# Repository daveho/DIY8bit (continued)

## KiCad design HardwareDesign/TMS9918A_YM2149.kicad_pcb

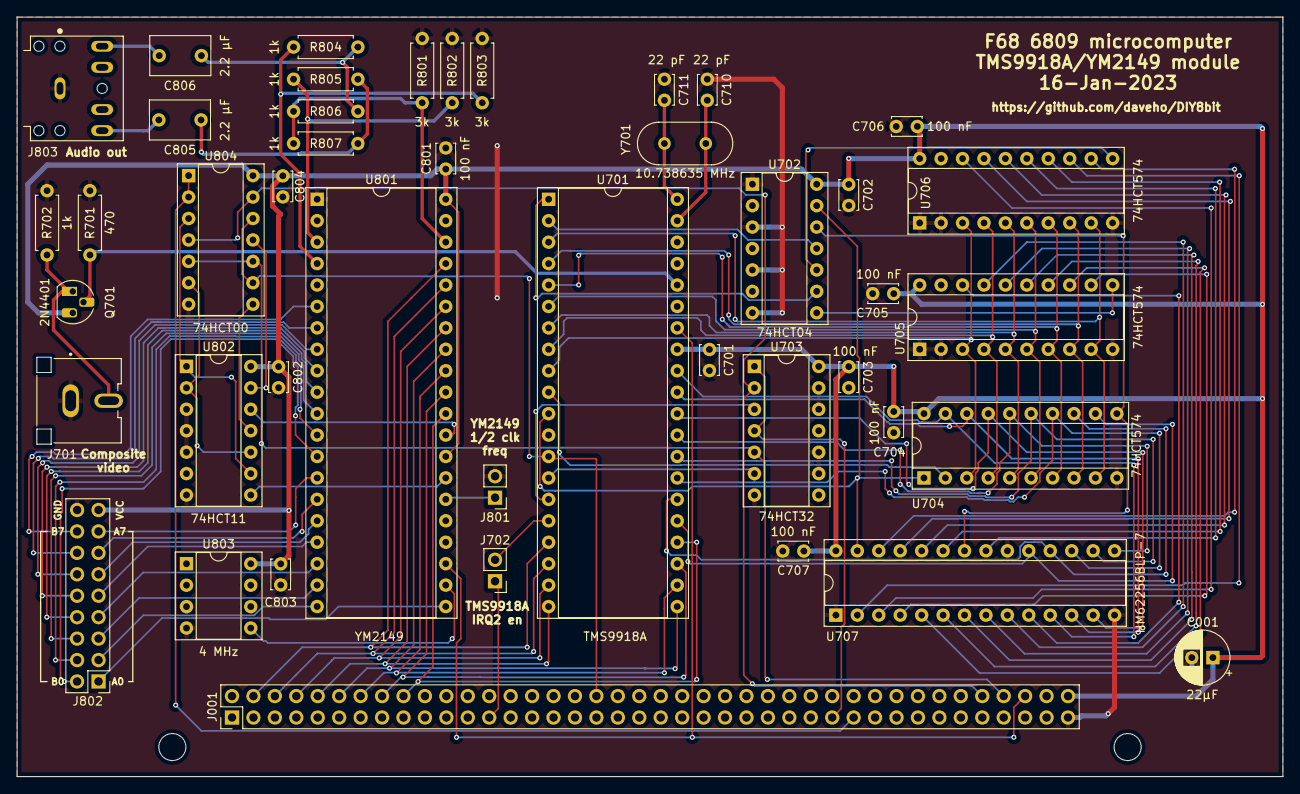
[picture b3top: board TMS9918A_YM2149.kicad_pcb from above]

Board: 2 copper layers, 150.0 x 90.0 mm, 44 parts (0 on the bottom side), 91 nets.

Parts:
C001: 22μF; CP_Radial_D6.3mm_P2.50mm
C701, C702, C703, C704, C705, C706, C707, C801, C802, C803, C804: 100 nF; C_Disc_D3.4mm_W2.1mm_P2.50mm
C710, C711: 22 pF; C_Disc_D3.4mm_W2.1mm_P2.50mm
C805, C806: 2.2 μF; C_Rect_L7.0mm_W4.5mm_P5.00mm
J001: Conn_02x40_Odd_Even; PinHeader_2x40_P2.54mm_Vertical
J701: RCJ-044; CUI_RCJ-044
J702, J801: Conn_01x02; PinHeader_1x02_P2.54mm_Vertical
J802: Conn_02x09_Odd_Even; PinHeader_2x09_P2.54mm_Vertical
J803: SJ1-3525N; CUI_SJ1-3525N
Q701: 2N4401; TO-92_HandSolder
R701: 470; R_Axial_DIN0207_L6.3mm_D2.5mm_P7.62mm_Horizontal
R702, R804, R805, R806, R807: 1k; R_Axial_DIN0207_L6.3mm_D2.5mm_P7.62mm_Horizontal
R801, R802, R803: 3k; R_Axial_DIN0207_L6.3mm_D2.5mm_P7.62mm_Horizontal
U701: TMS9918A; DIP-40_W15.24mm_Socket
U702: 74HCT04; DIP-14_W7.62mm_Socket
U703: 74HCT32; DIP-14_W7.62mm_Socket
U704, U705, U706: 74HCT574; DIP-20_W7.62mm_Socket
U707: HM62256BLP-7; DIP-28_W7.62mm_Socket
U801: YM2149; DIP-40_W15.24mm_Socket
U802: 74HCT11; DIP-14_W7.62mm_Socket
U803: 4 MHz; DIP-8_W7.62mm_Socket
U804: 74HCT00; DIP-14_W7.62mm_Socket
Y701: 10.738635 MHz; Crystal_HC18-U_Vertical

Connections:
/A0: J001.36, U701.13 (MODE), U804.9, U804.12
/D0: J001.4, U701.17 (CD7), U801.37 (DA0)
/D1: J001.6, U701.18 (CD6), U801.36 (DA1)
/D2: J001.8, U701.19 (CD5), U801.35 (DA2)
/D3: J001.10, U701.20 (CD4), U801.34 (DA3)
/D4: J001.12, U701.21 (CD3), U801.33 (DA4)
/D5: J001.14, U701.22 (CD2), U801.32 (DA5)
/D6: J001.16, U701.23 (CD1), U801.31 (DA6)
/D7: J001.18, U701.24 (CD0), U801.30 (DA7)
/TMS9918ADisplay/AD0: U701.10 (AD0), U704.2 (D0)
/TMS9918ADisplay/AD1: U701.9 (AD1), U704.3 (D1), U705.3 (D1), U706.3 (D1)
/TMS9918ADisplay/AD2: U701.8 (AD2), U704.4 (D2), U705.4 (D2), U706.4 (D2)
/TMS9918ADisplay/AD3: U701.7 (AD3), U704.5 (D3), U705.5 (D3), U706.5 (D3)
/TMS9918ADisplay/AD4: U701.6 (AD4), U704.6 (D4), U705.6 (D4), U706.6 (D4)
/TMS9918ADisplay/AD5: U701.5 (AD5), U704.7 (D5), U705.7 (D5), U706.7 (D5)
/TMS9918ADisplay/AD6: U701.4 (AD6), U704.8 (D6), U705.8 (D6), U706.8 (D6)
/TMS9918ADisplay/AD7: U701.3 (AD7), U704.9 (D7), U705.9 (D7), U706.9 (D7)
/TMS9918ADisplay/VA0: U705.18 (Q1), U707.10 (A0)
/TMS9918ADisplay/VA1: U705.17 (Q2), U707.9 (A1)
/TMS9918ADisplay/VA2: U705.16 (Q3), U707.8 (A2)
/TMS9918ADisplay/VA3: U705.15 (Q4), U707.7 (A3)
/TMS9918ADisplay/VA4: U705.14 (Q5), U707.6 (A4)
/TMS9918ADisplay/VA5: U705.13 (Q6), U707.5 (A5)
/TMS9918ADisplay/VA6: U705.12 (Q7), U707.4 (A6)
/TMS9918ADisplay/VA7: U706.18 (Q1), U707.3 (A7)
/TMS9918ADisplay/VA8: U706.17 (Q2), U707.25 (A8)
/TMS9918ADisplay/VA9: U706.16 (Q3), U707.24 (A9)
/TMS9918ADisplay/VA10: U706.15 (Q4), U707.21 (A10)
/TMS9918ADisplay/VA11: U706.14 (Q5), U707.23 (A11)
/TMS9918ADisplay/VA12: U706.13 (Q6), U707.2 (A12)
/TMS9918ADisplay/VA13: U706.12 (Q7), U707.26 (A13)
/TMS9918ADisplay/VD0: U701.32 (RD0), U704.19 (Q0), U707.11 (D0)
/TMS9918ADisplay/VD1: U701.31 (RD1), U704.18 (Q1), U707.12 (D1)
/TMS9918ADisplay/VD2: U701.30 (RD2), U704.17 (Q2), U707.13 (D2)
/TMS9918ADisplay/VD3: U701.29 (RD3), U704.16 (Q3), U707.15 (D3)
/TMS9918ADisplay/VD4: U701.28 (RD4), U704.15 (Q4), U707.16 (D4)
/TMS9918ADisplay/VD5: U701.27 (RD5), U704.14 (Q5), U707.17 (D5)
/TMS9918ADisplay/VD6: U701.26 (RD6), U704.13 (Q6), U707.18 (D6)
/TMS9918ADisplay/VD7: U701.25 (RD7), U704.12 (Q7), U707.19 (D7)
/TMS9918ADisplay/VR/~W: U701.11 (R/~W), U702.13, U704.1 (OE), U707.27 (~WE)
/TMS9918ADisplay/V~R/W: U702.12, U704.11 (Cp), U707.22 (~OE)
/TMS9918ADisplay/~CAS: U701.2 (~CAS), U702.11
/TMS9918ADisplay/~RAS: U701.1 (~RAS), U702.9
/TMS9918ADisplay/~VDPRD: U701.15 (~CSR), U703.3
/TMS9918ADisplay/~VDPWR: U701.14 (~CSW), U703.6
/YM2149_Sound/ANLG_A: R803.1, R804.1, U801.4 (ANLG_A)
/YM2149_Sound/ANLG_B: R802.1, R805.1, U801.3 (ANLG_B)
/YM2149_Sound/ANLG_C: R801.1, R806.1, R807.1, U801.38 (ANLG_C)
/YM2149_Sound/BC1: U801.29 (BC1), U802.12
/YM2149_Sound/BDIR: U801.27 (BDIR), U802.8
/YM2149_Sound/IOA0: J802.1, U801.21 (IOA0)
/YM2149_Sound/IOA1: J802.3, U801.20 (IOA1)
/YM2149_Sound/IOA2: J802.5, U801.19 (IOA2)
/YM2149_Sound/IOA3: J802.7, U801.18 (IOA3)
/YM2149_Sound/IOA4: J802.9, U801.17 (IOA4)
/YM2149_Sound/IOA5: J802.11, U801.16 (IOA5)
/YM2149_Sound/IOA6: J802.13, U801.15 (IOA6)
/YM2149_Sound/IOA7: J802.15, U801.14 (IOA7)
/YM2149_Sound/IOB0: J802.2, U801.13 (IOB0)
/YM2149_Sound/IOB1: J802.4, U801.12 (IOB1)
/YM2149_Sound/IOB2: J802.6, U801.11 (IOB2)
/YM2149_Sound/IOB3: J802.8, U801.10 (IOB3)
/YM2149_Sound/IOB4: J802.10, U801.9 (IOB4)
/YM2149_Sound/IOB5: J802.12, U801.8 (IOB5)
/YM2149_Sound/IOB6: J802.14, U801.7 (IOB6)
/YM2149_Sound/IOB7: J802.16, U801.6 (IOB7)
/YM2149_Sound/RING: C806.1, R804.2, R806.2
/YM2149_Sound/TIP: C805.1, R805.2, R807.2
/~IODEV5: J001.57, U703.1, U703.4
/~IODEV6: J001.59, U804.1, U804.2
/~IRQ2: J001.25, J702.1
/~RMEM: J001.72, U703.2, U804.4, U804.13
/~RST: J001.76, U701.34 (~RESET/SYNC), U801.23 (-RST)
/~WMEM: J001.74, U703.5, U804.5, U804.10
GND: C001.2, C701.2, C702.2, C703.2, C704.2, C705.2, C706.2, C707.2, C710.1, C711.1, C801.2, C802.2, C803.2, C804.2, J001.79, J701.1, J801.2, J802.18, J803.1, R701.2, R702.2, R801.2, R802.2, R803.2, U701.12 (VSS), U702.1, U702.3, U702.5, U702.7 (GND), U703.7 (GND), U703.9, U703.10, U703.12, U703.13, U704.10 (GND), U705.1 (OE), U705.2 (D0), U705.10 (GND), U706.1 (OE), U706.2 (D0), U706.10 (GND), U707.1 (A14), U707.14 (GND), U707.20 (~CS), U801.1 (GND), U802.3, U802.4, U802.5, U802.7 (GND), U803.4 (GND), U804.7 (GND)
unnamed: C710.2, U701.39 (XTAL1), Y701.2
unnamed: C711.2, U701.40 (XTAL2), Y701.1
unnamed: C805.2, J803.2
unnamed: C806.2, J803.3
unnamed: J701.2, Q701.1 (E), R702.1
unnamed: J702.2, U701.16 (~INT)
unnamed: J801.1, U801.26 (-SEL)
unnamed: Q701.2 (B), R701.1, U701.36 (COMVID)
unnamed: U702.8, U705.11 (Cp)
unnamed: U702.10, U706.11 (Cp)
unnamed: U801.22 (CLK), U803.5 (CLK)
unnamed: U802.1, U802.9, U804.3
unnamed: U802.2, U802.10, U804.6
unnamed: U802.11, U804.8
unnamed: U802.13, U804.11
VCC: C001.1, C701.1, C702.1, C703.1, C704.1, C705.1, C706.1, C707.1, C801.1, C802.1, C803.1, C804.1, J001.80, J802.17, Q701.3 (C), U701.33 (VCC), U702.14 (VCC), U703.14 (VCC), U704.20 (VCC), U705.20 (VCC), U706.20 (VCC), U707.28 (VCC), U801.28 (BC2), U801.40 (VCC), U802.14 (VCC), U803.8 (VCC), U804.14 (VCC)

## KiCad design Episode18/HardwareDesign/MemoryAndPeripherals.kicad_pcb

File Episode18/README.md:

# DIY 8-bit computer, Episode 18

Link to video: <https://youtu.be/xi_Eh6LUsHY>

In this video, I assemble and test a PCB for the memory and peripherals module
for the F68 6809 computer system.  The PCB replaces the original hand-wired
prototype version of the module, and adds support for RS-232 serial
communication using a MAX232 transceiver chip.

The [HardwareDesign](HardwareDesign) directory has the schematics and PCB
designs.  I updated the PCB design for the memory and peripherals module
to fix the minor issue I discovered in the video where one of the clock
inputs of the 82C54 timer/counter chip was not connected.

The [Code](Code) directory has the updated code for the monitor program,
which adds a `k` command to display some sweet ASCII art.

## Serial communication headers

The PCB has two 5-pin headers for serial communication.

The monitor program is hard-coded for 9600 bps, 8N1, so that's what the
remote (communicating) device should be configured for.

### Labeling of pins

Note that the silkscreen markings for the individual pins on the two
serial communications headers (TTL serial and RS-232) are
describing a signal of the *remote* device, i.e., the device that
the 6809 system will be communicating with.  For example, the pin labeled
`Rx` should be connected to the Rx (receive) input on the remote device, and
is driven by the Tx (transmit) pin on the 6809 system's 63B50 UART.

I hope this makes sense!

### TTL serial header

The header labeled "TTL serial" uses standard TTL-level signals.

The TTL serial header may be connected to a USB serial adapter as follows:

TTL serial header pin | USB serial adapter pin
--------------------- | ----------------------
GND                   | GND
RTS                   | RTS
CTS                   | CTS
Rx                    | Rx
Tx                    | Tx

### RS-232 header

The header labeled "RS-232" uses a MAX232 chip for serial communication using
RS-232 level signals.  As with the "TTL serial" header, the silkscreen labels
for the pins refer to the remote device, not the 6809 system.

How these header pins are connected will depend on two factors:

* whether the remote device is DTE (Data Terminal Equipment) or DCE (Data
  Communication Equipment)
* whether the RS-232 cable is straight through or null modem

PCs and serial terminals are both DTE devices.

The following tables show how to write the 5-pin RS-232 header on the PCB
to a 9-pin (D-sub) serial connector.

For connection to a DTE device using a straight-through cable, or a DCE device
using a null modem cable:

RS-232 header pin | Serial connector pin
----------------- | --------------------
GND               | 5
RTS               | 7
CTS               | 8
Rx                | 2
Tx                | 3

For connection to a DCE device using a straight-through cable, or a DTE
device using a null modem cable:

RS-232 header pin | Serial connector pin
----------------- | --------------------
GND               | 5
RTS               | 8
CTS               | 7
Rx                | 3
Tx                | 2

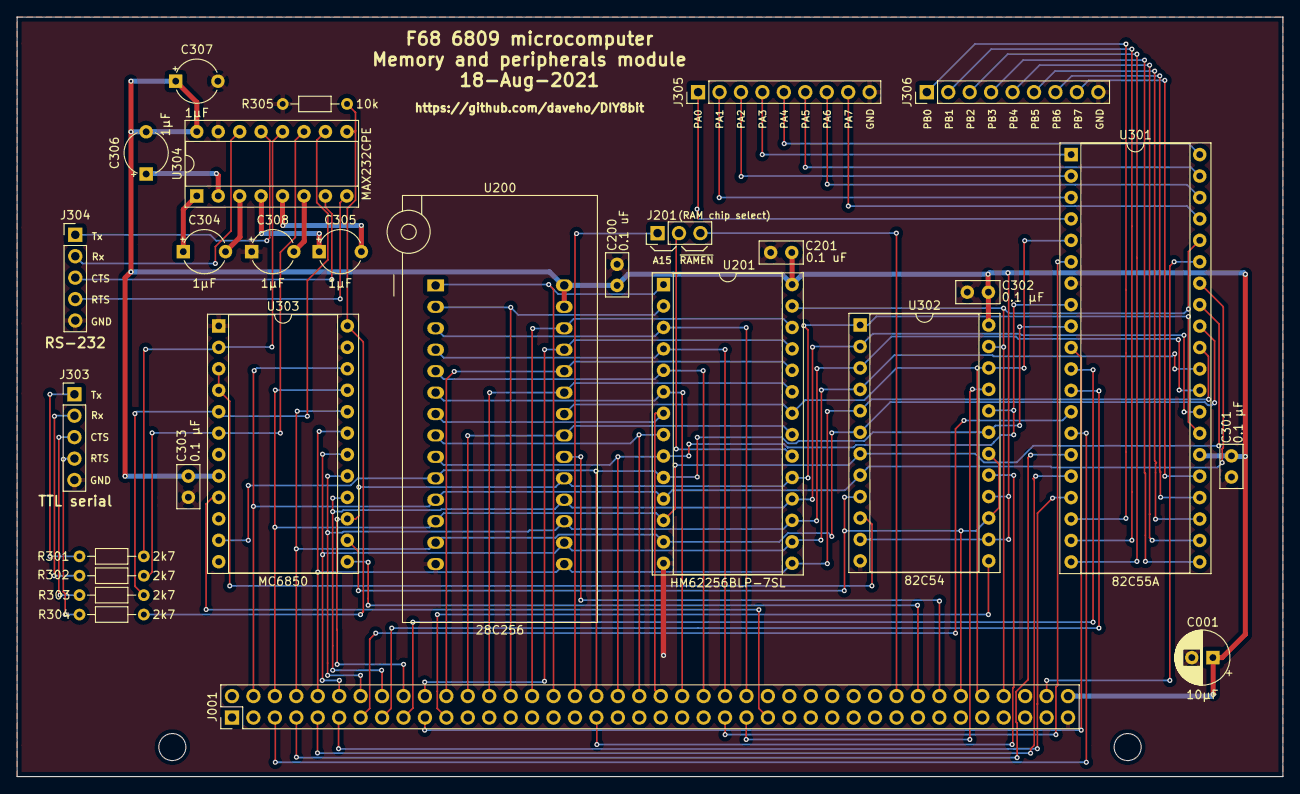
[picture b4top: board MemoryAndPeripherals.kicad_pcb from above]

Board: 2 copper layers, 150.0 x 90.0 mm, 28 parts (0 on the bottom side), 82 nets.

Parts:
C001: 10μF; CP_Radial_D6.3mm_P2.50mm
C200, C201: 0.1 uF; C_Disc_D5.0mm_W2.5mm_P2.50mm
C301, C302, C303: 0.1 μF; C_Disc_D5.0mm_W2.5mm_P2.50mm
C304, C305, C306, C307, C308: 1μF; CP_Radial_Tantal_D5.0mm_P5.00mm
J001: Conn_02x40_Odd_Even; PinHeader_2x40_P2.54mm_Vertical
J201: Conn_01x03; PinHeader_1x03_P2.54mm_Vertical
J303, J304: Conn_01x05; PinHeader_1x05_P2.54mm_Vertical
J305, J306: Conn_01x09; PinHeader_1x09_P2.54mm_Vertical
R301, R302, R303, R304: 2k7; R_Axial_DIN0204_L3.6mm_D1.6mm_P7.62mm_Horizontal
R305: 10k; R_Axial_DIN0204_L3.6mm_D1.6mm_P7.62mm_Horizontal
U200: 28C256; DIP_Socket-28_W11.9_W12.7_W15.24_W17.78_W18.5_3M_228-1277-0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
U201: HM62256BLP-7SL; DIP-28_W15.24mm_Socket
U301: 82C55A; DIP-40_W15.24mm_Socket
U302: 82C54; DIP-24_W15.24mm_Socket
U303: MC6850; DIP-24_W15.24mm_Socket
U304: MAX232CPE; DIP-16_W7.62mm_Socket

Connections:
/A0: J001.36, U200.10, U201.10, U301.9, U302.19, U303.11
/A1: J001.38, U200.9, U201.9, U301.8, U302.20
/A2: J001.40, U200.8, U201.8
/A3: J001.42, U200.7, U201.7
/A4: J001.44, U200.6, U201.6
/A5: J001.46, U200.5, U201.5
/A6: J001.48, U200.4, U201.4
/A7: J001.50, U200.3, U201.3
/A8: J001.20, U200.25, U201.25
/A9: J001.22, U200.24, U201.24
/A10: J001.24, U200.21, U201.21
/A11: J001.26, U200.23, U201.23
/A12: J001.28, U200.2, U201.2
/A13: J001.30, U200.26, U201.26
/A14: J001.32, U200.1, U201.1
/A15: J001.34, J201.1
/CorePeriphs/-CTS: R304.2, R305.1, U303.24, U304.9
/CorePeriphs/-RTS: R303.2, U303.5, U304.10
/CorePeriphs/Ext_CTS: J304.3, U304.7
/CorePeriphs/Ext_RTS: J304.4, U304.8
/CorePeriphs/Ext_RxD: J304.2, U304.14
/CorePeriphs/Ext_TxD: J304.1, U304.13
/CorePeriphs/PA0: J305.1, U301.4
/CorePeriphs/PA1: J305.2, U301.3
/CorePeriphs/PA2: J305.3, U301.2
/CorePeriphs/PA3: J305.4, U301.1
/CorePeriphs/PA4: J305.5, U301.40
/CorePeriphs/PA5: J305.6, U301.39
/CorePeriphs/PA6: J305.7, U301.38
/CorePeriphs/PA7: J305.8, U301.37
/CorePeriphs/PB0: J306.1, U301.18
/CorePeriphs/PB1: J306.2, U301.19
/CorePeriphs/PB2: J306.3, U301.20
/CorePeriphs/PB3: J306.4, U301.21
/CorePeriphs/PB4: J306.5, U301.22
/CorePeriphs/PB5: J306.6, U301.23
/CorePeriphs/PB6: J306.7, U301.24
/CorePeriphs/PB7: J306.8, U301.25
/CorePeriphs/RxD: R301.2, U303.2, U304.12
/CorePeriphs/TxD: R302.2, U303.6, U304.11
/D0: J001.4, U200.11, U201.11, U301.34, U302.8, U303.22
/D1: J001.6, U200.12, U201.12, U301.33, U302.7, U303.21
/D2: J001.8, U200.13, U201.13, U301.32, U302.6, U303.20
/D3: J001.10, U200.15, U201.15, U301.31, U302.5, U303.19
/D4: J001.12, U200.16, U201.16, U301.30, U302.4, U303.18
/D5: J001.14, U200.17, U201.17, U301.29, U302.3, U303.17
/D6: J001.16, U200.18, U201.18, U301.28, U302.2, U303.16
/D7: J001.18, U200.19, U201.19, U301.27, U302.1, U303.15
/E: J001.70, U302.9, U302.15, U302.18, U303.14
/IRQ3: J001.21, U302.13
/PC0: J001.5, U301.14
/PC1: J001.7, U301.15
/PC2: J001.9, U301.16
/PC3: J001.11, U301.17
/PC4: J001.13, U301.13
/PC5: J001.15, U301.12
/PC6: J001.17, U301.11
/PC7: J001.19, U301.10
/RST: J001.78, U301.35
/R~W~: J001.66, U303.13
/TCOUNT2: J001.35, U302.17
/~IODEV0: J001.47, U301.6
/~IODEV1: J001.49, U302.21
/~IODEV2: J001.51, U303.9
/~RAMEN~: J001.64, J201.3
/~RMEM~: J001.72, U200.22, U201.22, U301.5, U302.22
/~ROMEN~: J001.68, U200.20
/~WMEM~: J001.74, U201.27, U301.36, U302.23
GND: C001.2, C200.2, C201.2, C301.2, C302.2, C303.2, C307.2, C308.1, J001.79, J303.5, J304.5, J305.9, J306.9, R305.2, U200.14, U201.14, U301.7, U302.12, U303.1, U303.23, U304.15
unnamed: C304.1, U304.1
unnamed: C304.2, U304.3
unnamed: C305.1, U304.4
unnamed: C305.2, U304.5
unnamed: C306.1, U304.2
unnamed: C308.2, U304.6
unnamed: J201.2, U201.20
unnamed: J303.1, R301.1
unnamed: J303.2, R302.1
unnamed: J303.3, R303.1
unnamed: J303.4, R304.1
unnamed: U302.10, U303.3, U303.4
VCC: C001.1, C200.1, C201.1, C301.1, C302.1, C303.1, C306.2, C307.1, J001.80, U200.27, U200.28, U201.28, U301.26, U302.11, U302.14, U302.16, U302.24, U303.8, U303.10, U303.12, U304.16

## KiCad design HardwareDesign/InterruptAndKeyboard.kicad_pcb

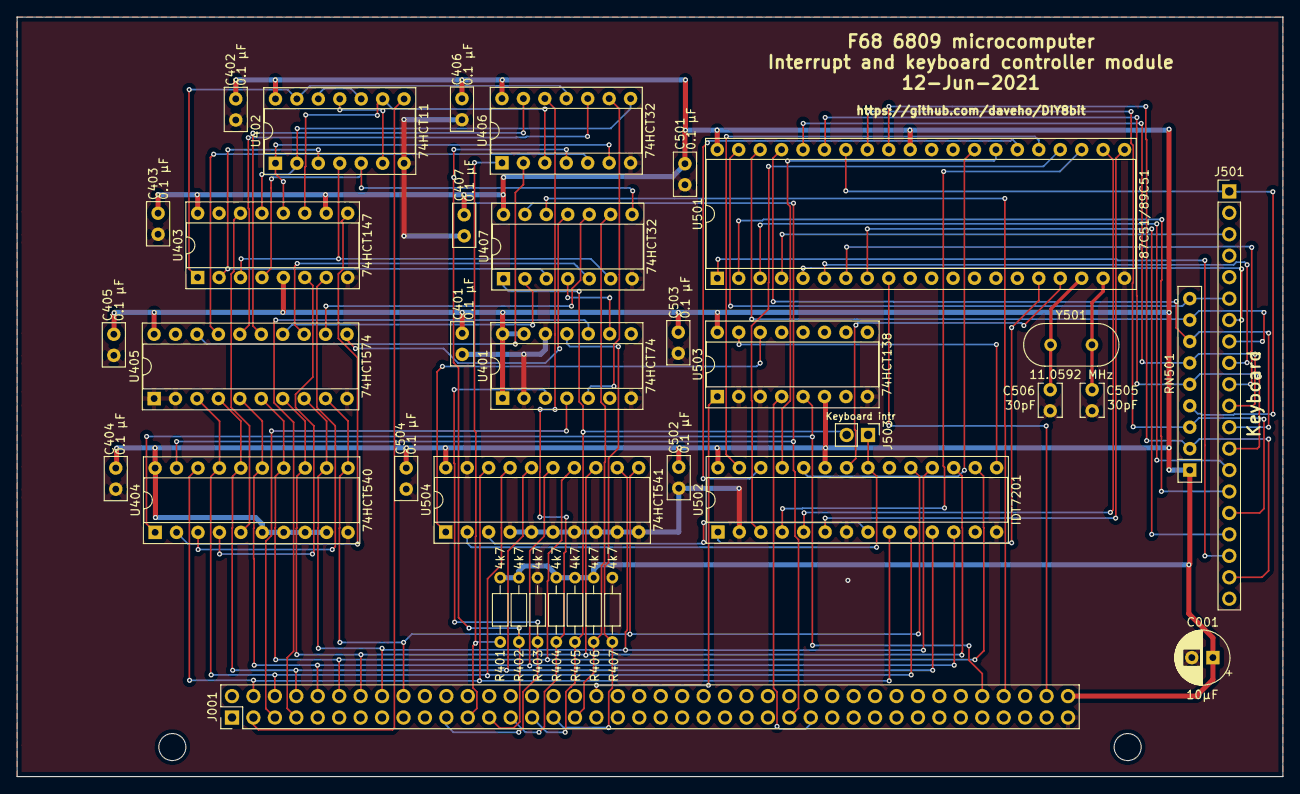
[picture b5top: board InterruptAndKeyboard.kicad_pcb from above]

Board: 2 copper layers, 150.0 x 90.0 mm, 37 parts (0 on the bottom side), 81 nets.

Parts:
C001: 10μF; CP_Radial_D6.3mm_P2.50mm
C401, C402, C403, C404, C405, C406, C407, C501, C502, C503, C504: 0.1 μF; C_Disc_D5.0mm_W2.5mm_P2.50mm
C505, C506: 30pF; C_Disc_D3.8mm_W2.6mm_P2.50mm
J001: Conn_02x40_Odd_Even; PinHeader_2x40_P2.54mm_Vertical
J501: Conn_01x20; PinHeader_1x20_P2.54mm_Vertical
J503: Conn_01x02; PinHeader_1x02_P2.54mm_Vertical
R401, R402, R403, R404, R405, R406, R407: 4k7; R_Axial_DIN0204_L3.6mm_D1.6mm_P7.62mm_Horizontal
RN501: R_Network08; R_Array_SIP9
U401: 74HCT74; DIP-14_W7.62mm_Socket
U402: 74HCT11; DIP-14_W7.62mm_Socket
U403: 74HCT147; DIP-16_W7.62mm_Socket
U404: 74HCT540; DIP-20_W7.62mm_Socket
U405: 74HCT574; DIP-20_W7.62mm_Socket
U406, U407: 74HCT32; DIP-14_W7.62mm_Socket
U501: 87C51/89C51; DIP-40_W15.24mm_Socket
U502: IDT7201; DIP-28_W7.62mm_Socket
U503: 74HCT138; DIP-16_W7.62mm_Socket
U504: 74HCT541; DIP-20_W7.62mm_Socket
Y501: 11.0592 MHz; Crystal_HC18-U_Vertical

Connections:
/A0: J001.36, U503.1
/D0: J001.4, U404.18, U502.9, U504.18
/D1: J001.6, U404.17, U405.3, U502.10, U504.17
/D2: J001.8, U404.16, U405.4, U502.11, U504.16
/D3: J001.10, U404.15, U405.5, U502.12, U504.15
/D4: J001.12, U404.14, U405.6, U502.16, U504.14
/D5: J001.14, U404.13, U405.7, U502.17, U504.13
/D6: J001.16, U404.12, U405.8, U502.18, U504.12
/D7: J001.18, U404.11, U405.9, U502.19, U504.11
/IRQ3: J001.21, R403.1, U401.3
/IRQ6: J001.31, R407.1, U401.11
/Interrupts/~IRQ3~: U401.5, U406.9
/Interrupts/~IRQ6~: U401.9, U407.4
/Keyboard/COL0: J501.18, U501.1
/Keyboard/COL1: J501.15, U501.2
/Keyboard/COL2: J501.14, U501.3
/Keyboard/COL3: J501.3, U501.4
/Keyboard/COL4: J501.7, U501.5
/Keyboard/COL5: J501.9, U501.6
/Keyboard/COL6: J501.10, U501.7
/Keyboard/COL7: J501.17, U501.8
/Keyboard/EF: J503.1, U502.21, U504.2
/Keyboard/FF: U502.8, U504.3
/Keyboard/ROW0: J501.6, RN501.9, U501.39
/Keyboard/ROW1: J501.8, RN501.8, U501.38
/Keyboard/ROW2: J501.12, RN501.7, U501.37
/Keyboard/ROW3: J501.11, RN501.6, U501.36
/Keyboard/ROW4: J501.13, RN501.5, U501.35
/Keyboard/ROW5: J501.1, RN501.4, U501.34
/Keyboard/ROW6: J501.16, RN501.3, U501.33
/Keyboard/ROW7: J501.19, RN501.2, U501.32
/Keyboard/SCDAT0: U501.21, U502.6
/Keyboard/SCDAT1: U501.22, U502.5
/Keyboard/SCDAT2: U501.23, U502.4
/Keyboard/SCDAT3: U501.24, U502.3
/Keyboard/SCDAT4: U501.25, U502.27
/Keyboard/SCDAT5: U501.26, U502.26
/Keyboard/SCDAT6: U501.27, U502.25
/Keyboard/SCDAT7: U501.28, U502.24
/Keyboard/~FIFO_CLR: U501.17, U502.22
/Keyboard/~FIFO_WR: U501.16, U502.1
/Keyboard/~RD_CTRL: U503.14, U504.1
/Keyboard/~RD_DATA: U502.15, U503.15
/PC0: J001.5, U401.4
/PC1: J001.7, U401.10
/RST: J001.78, U501.9
/~IODEV3: J001.53, U404.19, U407.13
/~IODEV4: J001.55, U503.4
/~IRQ: J001.3, U402.8
/~IRQ1~: J001.23, R401.2, U406.1
/~IRQ2~: J001.25, R402.2, U406.4
/~IRQ4~: J001.27, R404.2, U406.12
/~IRQ5~: J001.29, J503.2, R405.2, U407.1
/~IRQ7~: J001.33, R406.2, U407.9
/~RMEM~: J001.72, U404.1, U503.5
/~WMEM~: J001.74, U407.12
GND: C001.2, C401.2, C402.2, C403.2, C404.2, C405.2, C406.2, C407.2, C501.2, C502.2, C503.2, C504.2, C505.1, C506.1, J001.79, R403.2, R407.2, U401.2, U401.7, U401.12, U402.7, U403.8, U404.10, U405.1, U405.2, U405.10, U406.7, U407.7, U501.20, U502.2, U502.7, U502.14, U503.2, U503.3, U503.8, U504.4, U504.5, U504.6, U504.7, U504.8, U504.9, U504.10, U504.19
unnamed: C505.2, U501.19, Y501.2
unnamed: C506.2, U501.18, Y501.1
unnamed: U402.1, U403.12, U406.6
unnamed: U402.2, U403.13, U406.8
unnamed: U402.3, U403.2, U407.3
unnamed: U402.4, U403.3, U407.6
unnamed: U402.5, U403.4, U407.8
unnamed: U402.9, U403.11, U406.3
unnamed: U402.10, U402.12
unnamed: U402.6, U402.11
unnamed: U402.13, U403.1, U406.11
unnamed: U403.6, U404.4
unnamed: U403.7, U404.3
unnamed: U403.9, U404.2
unnamed: U403.14, U404.5
unnamed: U405.11, U407.11
unnamed: U405.12, U407.10
unnamed: U405.13, U407.5
unnamed: U405.14, U407.2
unnamed: U405.15, U406.13
unnamed: U405.16, U406.10
unnamed: U405.17, U406.5
unnamed: U405.18, U406.2
VCC: C001.1, C401.1, C402.1, C403.1, C404.1, C405.1, C406.1, C407.1, C501.1, C502.1, C503.1, C504.1, J001.80, R401.1, R402.1, R404.1, R405.1, R406.1, RN501.1, U401.1, U401.13, U401.14, U402.14, U403.5, U403.10, U403.16, U404.6, U404.7, U404.8, U404.9, U404.20, U405.20, U406.14, U407.14, U501.31, U501.40, U502.23, U502.28, U503.6, U503.16, U504.20

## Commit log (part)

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2021-05-26 minor correction
2021-05-26 info for Episode 14
2021-05-30 first FPGA experiment
    Generate 6 MHz square wave by dividing the internal
    48 MHz high frequency oscillator signal by 8.
2021-06-01 initial VGA bracket design (bottom part)
2021-06-01 component symbol for Upduino 3.0
2021-06-02 initial display circuit
    The display isn't interfaced with the system yet.
    Initial goal is to generate a valid 800x600 SVGA signal.
    Added a footprint for the Upduino 3.0, which is DIP-48,
    but 0.7" wide rather than the standard 0.6".
2021-06-03 corrected Upduino 3.0 pin assignments
    The 12MHz and GND3 pins were accidentally reversed
    on the silkscreen.
2021-06-03 generate hsync
    Kind of works, but there seems to be a lot of unexpected
    jitter.
2021-06-04 successfully use external oscillator
    Dividing external 12 MHz oscillator signal by 2 yields a
    6 MHz square wave. This appears to be rock solid, and free
    from the jitter which is seen when using the internal
    high frequency oscillator as a clock.
2021-06-04 working on hsync generation
2021-06-04 hsync generation actually works!!!
    For some reason, making hcount a 16-bit register did the
    trick. I saw *very* strange behavior when hcount was an
    11-bit register, which in theory should be large enough.
2021-06-05 generate vsync and pixel colors
    Vsync looks correct on the scope.
    Pixels are just a solid color for the moment.
2021-06-07 save hardware design for Episode 15
2021-06-07 fix text of directory links
2021-06-07 bracket to help backplane connector to fit securely
2021-06-07 model prints ok without supports?
2021-06-10 route ~IODEV0 through ~IODEV4 to backplane connector
    For some reason, the pins of the 74HCT138 weren't labeled
    with the same nets as the corresponding pins on the backplane
    connector, even though they have continuity on the schematic.
2021-06-10 copy current hardware design to Episode16 directory
2021-06-10 README.md for Episode 16
2021-06-11 start PCB for memory and peripherals
2021-06-11 routed more signals
2021-06-12 all non-GND signals routed
    Removed all explicit traces/vias for GND, since there
    will be a ground plane on both layers.
2021-06-12 add URL, minor silkscreen tweak
    Is ready to fab?
2021-06-12 silkscreen tweaks
2021-06-12 more routing...
2021-06-12 all connections routed?
2021-06-23 added ~RAMEN~ backplane signals
    Added a jumper so that the RAM chip can be configured
    to use either A15 or ~RAMEN~ as its enable.
    This change allows a CPU/glue logic module to have flexibility
    regarding where the RAM is mapped.
2021-06-23 made a couple of silkscreen designators larger
2021-06-23 generate gerbers for intr/kbd controllers
2021-06-23 not sure what changed?
2021-06-24 made display circuit a test using an Arduino Nano
    Once communication between the Arduino and the FPGA
    via the FIFO is working, then it will make sense to work
    on interfacing with the actual host system.
2021-06-25 minor changes to display test circuit
2021-07-31 rename Episode17 directory as Episode18
    Episode 17 will be testing the revised CPU/glue logic
    PCB.
2021-08-01 fix a link
2021-08-23 rename Episode18 as Episode19
    Episode18 will be assembling and testing the memory and
    peripheral PCB.
2021-08-24 add pdf schematic
2021-09-04 rename Episode19 as Episode1a
2021-09-06 screenshot from video
2021-09-06 forgot to add screenshot
2021-12-22 more detailed planning for display controller host interface
    Enumerated all of the signals in a spreadsheet, making
    it explicit which ones require 5V to 3.3V level conversion.
    Renamed signals so that there is a more consistent naming
    scheme.
2021-12-23 initial experiment to add a reset input
    For some reason, the entire design doesn't work unless the
    input signal is written to an output register connected to
    a GPIO pin. I have no idea why this is necessary.
2021-12-24 writing to nrst_out does seem to be necessary
2021-12-25 added pull-up resistors to data inputs of U604
    This ensures that the voltages are at a valid logic
    level even when the FIFO is not driving data on its
    outputs.
    This should also be useful if we add a second FIFO
    (e.g., to split command and data streams.)
2021-12-27 delay to make sure data is stable
2022-01-01 experiment to clock the design at 120 MHz
2022-01-02 complete rewrite of Arduino sketch
    The manual reset button now completely resets the
    data generation.
    Added a hack so that only one data value is written.
    I was debugging an issue where the empty flag wasn't
    re-asserted after reading a single data value, which
    obviously caused major problems for the read logic
2022-01-03 make tick counter 16 bits, misc. cleanups
2022-01-03 implemented a proper shared register module
    Use this for communication from the FIFO-reading state
    machine and the command-processing state machine.
2022-01-03 FIFO command bytes control blue color values
2022-01-03 I think this design actually worked
2022-01-03 some additional info
2022-01-09 use syncgen for vsync
2022-01-09 maybe even slightly more accurate vertical timing?
2022-01-15 generate pixels from buffer in block RAM
    Reading from the block RAM seems to work fine.
    However, when the command code tries to write to the
    block RAM, icestorm fails to infer that the memory
    should be a block RAM. (Actually, I'm not 100%
    confident that it's inferring this correctly in the
    case where there are only reads from the buffer.)
2022-01-16 added header comment explaining the experiment
2022-01-17 HOLY CRAP WE ARE DISPLAYING PIXEL DATA
    Data from the command FIFO is successfully copied into the
    line buffer BRAM, and in turn the contents of the line buffer
    BRAM are used to control generation of foreground/background
    pixel colors.
    Even better, the design could even work at an internal clock
    frequency of 40 MHz, because loading data from the BRAM and
2022-01-23 README for episode 1B
2022-07-02 experiment 2: rasterize groups of 8 fg/bg pixels
    This is basically the last stage of the text mode pipeline.
2022-07-03 added another debug LED
2022-07-03 modified shared_reg so that has_data is cleared eagerly
    This fixes an issue where the consumer would see the
    data in the shared register twice. (I think!)
2022-07-04 explain how to do slow data send
2022-07-04 experiment 4, load font data to display controller
    It seems to work? It's somewhat hard to know, since the
    font data is just inside block RAM, and isn't used for
    anything yet. However, it certainly looks like the
    Arduino is transferring the data, and the display
    controller does respond to commands after the font data
    is uploaded.
2022-07-07 load character data
2022-07-09 starting to work on character pixel generation
2022-07-12 more work accessing font data using rd/wr signals
2022-08-14 start README.md
    This is partially so I can remember what happened when.
2022-08-14 more debugging of character placement
    Verified that the last 256 bytes of the character RAM
    can be read, by loading different data into it than
    the first 256 bytes.
    It's clear that the first two columns of characters
    aren't displayed correctly. My suspicion is that ch_col
    and ch_row aren't being updated properly.
2022-08-14 rewriting hsync/vsync generation
    I think it's possible that pixel generation isn't properly
    synchronized with hsync and vsync.
2022-08-14 experiment to try to figure out sync and alignment issues
2022-08-14 minor cleanups
2022-08-14 more cleanups, getting there...
2022-08-14 set ch_row correctly for generating the top-left character
2022-08-20 start episode 1D
    First goal is to get the font data into SPRAM rather
    than block RAM.
2022-08-20 relocate font data to SPRAM: not working yet
2022-08-21 rewrites of shared_reg and readcommand
    I think these might be working better now?
    Much more testing needed.
2023-01-03 started TMS9918A display circuit
    It's really just a copy of a circuit created by Dr. Volt,
    https://github.com/michalin/TMS9918_Arduino
    Also, update project to KiCad 6 (which seems really nice
    so far!)
2023-01-05 start code for TMS9918A display
2023-01-06 code to load font data, untested
2023-01-06 starting to make progress on VDP init
    We can get into text mode. Still having issues loading
    the font and clearing VRAM. Maybe is timing related?
2023-01-06 a couple small cleanups
2023-01-07 improvements to the Episode 1D readme
2023-01-07 prepare to create PCB for TMS9918A module
2023-01-07 start working on YM2149 sound module
2023-01-08 YM2149 circuit ready for prototyping?
2023-01-09 2.2 uF film caps seem to work well for audio coupling
2023-01-10 reimplemented bus signal generation for YM2149
    The changes should help ensure that BC1 and BDIR only
    change from the inactive state when the chip is being
    accessed (for a read or write.)
2023-01-12 starter PCB for a system module
2023-01-12 fix some footprint assignments
2023-01-13 more arranging of components
2023-01-16 move J803 silkscreen
2023-01-16 more routing of TMS9918A address/data reg signals
    I think I have a viable strategy.
2023-01-16 all signals routed, DRC is clean
    Almost ready to fab?
2023-01-16 generated gerbers
2023-08-19 keyboard key to note mapping for synth program
2023-08-20 output table of freq reg vals
2023-08-20 added main loop (untested)
2023-09-24 fixed bugs reading keyboard scan codes
    kbd_poll polls for a keypress, but translates it into
    an ASCII code. Instead, we want to get the raw
    scancodes from the keyboard.
    Sound output doesn't work yet.
2024-06-25 VRAM test program
    Also cleaned up the programs Makefile a bit
2024-07-18 comment out TMS9918A code for now
2024-07-18 more work on hwvga routines, untested
2024-07-19 further modularization of monitor code
2024-07-19 add hwvga routines to offset table
    Also, add hwvga_set_font routine.
2024-07-19 dynamically find dependencies for programs
    Also, make sure that the assembler source file itself
    is included as a dependency.
2024-07-19 hwvga_compute_addr doesn't clobber Y
2024-07-19 add hwvga_clear_screen and hwvga_set_attr
2024-07-20 attempt to implement bulk copy to VRAM
    Doesn't really work. Probably would be best to
    start with a simpler approach that doesn't try to
    handle bank switching transparently.
2024-07-20 this is a pretty nice banner!
    Just need to print a fake prompt and move the cursor,
    and we have a pretty good demo of what the interactive
    UI might look like eventually.
2024-07-22 enable interrupts (needed for cursor blink)
2024-07-23 condense some end of line comments
2024-07-24 start display controller PCB
2024-07-24 attempt at footprint for SG-636P oscillator module
    From datasheet at
    https://www.mouser.com/datasheet/2/137/SG_636PCE_en-1003252.pdf
2024-07-24 fixed an incorrect footprint assignment
2024-07-24 eliminate DIP switch for initial VCOUNT
    Instead, hard-code initial VCOUNT to 485 (which is
    what the prototype sets it to.) This ensures that
    a VSync pulse clears the row begin address register
    before the first visible frame.
2024-07-25 more routing of traces
2024-07-25 removed some unneeded files
2024-07-26 redo connections between host A/D busses and VRAM
    The new approach uses the horizontal/vertical traces
    on different planes approach to (hopefully) allow
    for all of the signals the VRAM needs to be routed.
    (There are a lot of them!)
2024-07-26 getting close...mostly just the VRAM now
2024-07-27 routed VSync/HSync output voltage dividers
2024-07-27 fix more unconnected grounds
2024-07-27 fixed more unconnected ground plane fragments
2024-07-27 routed unconnected -RST traces
    Somehow KiCad failed to include these in the rats nest.
2024-07-27 fix another unrouted VRAM signal
    There were more of these than I expected.
2024-07-27 fixed silkscreen clipping in SG-636P footprint
2024-07-29 make some ground stitching vias line up nicely
2024-07-29 label the VRefresh/IRQ6 jumper
2024-07-29 generate gerbers
2024-08-01 bugfix: ReadoutA0 wasn't connected
    A wire was misplaced on the main sheet, which meant
    that the ReadoutA0 input of the VRAM module had no
    connection to the ReadoutA0 output from the Readout
    module.
    This will require a bodge wire on the 29-Jul-2024
    version of the PCB, but fortunately it will be a very
2025-12-30 initial schematic for FPGA display controller
2025-12-31 remove old version of FPGA display controller
    The "FPGADisplayController" module is the one that
    actually works.
2026-01-09 update copyright year
